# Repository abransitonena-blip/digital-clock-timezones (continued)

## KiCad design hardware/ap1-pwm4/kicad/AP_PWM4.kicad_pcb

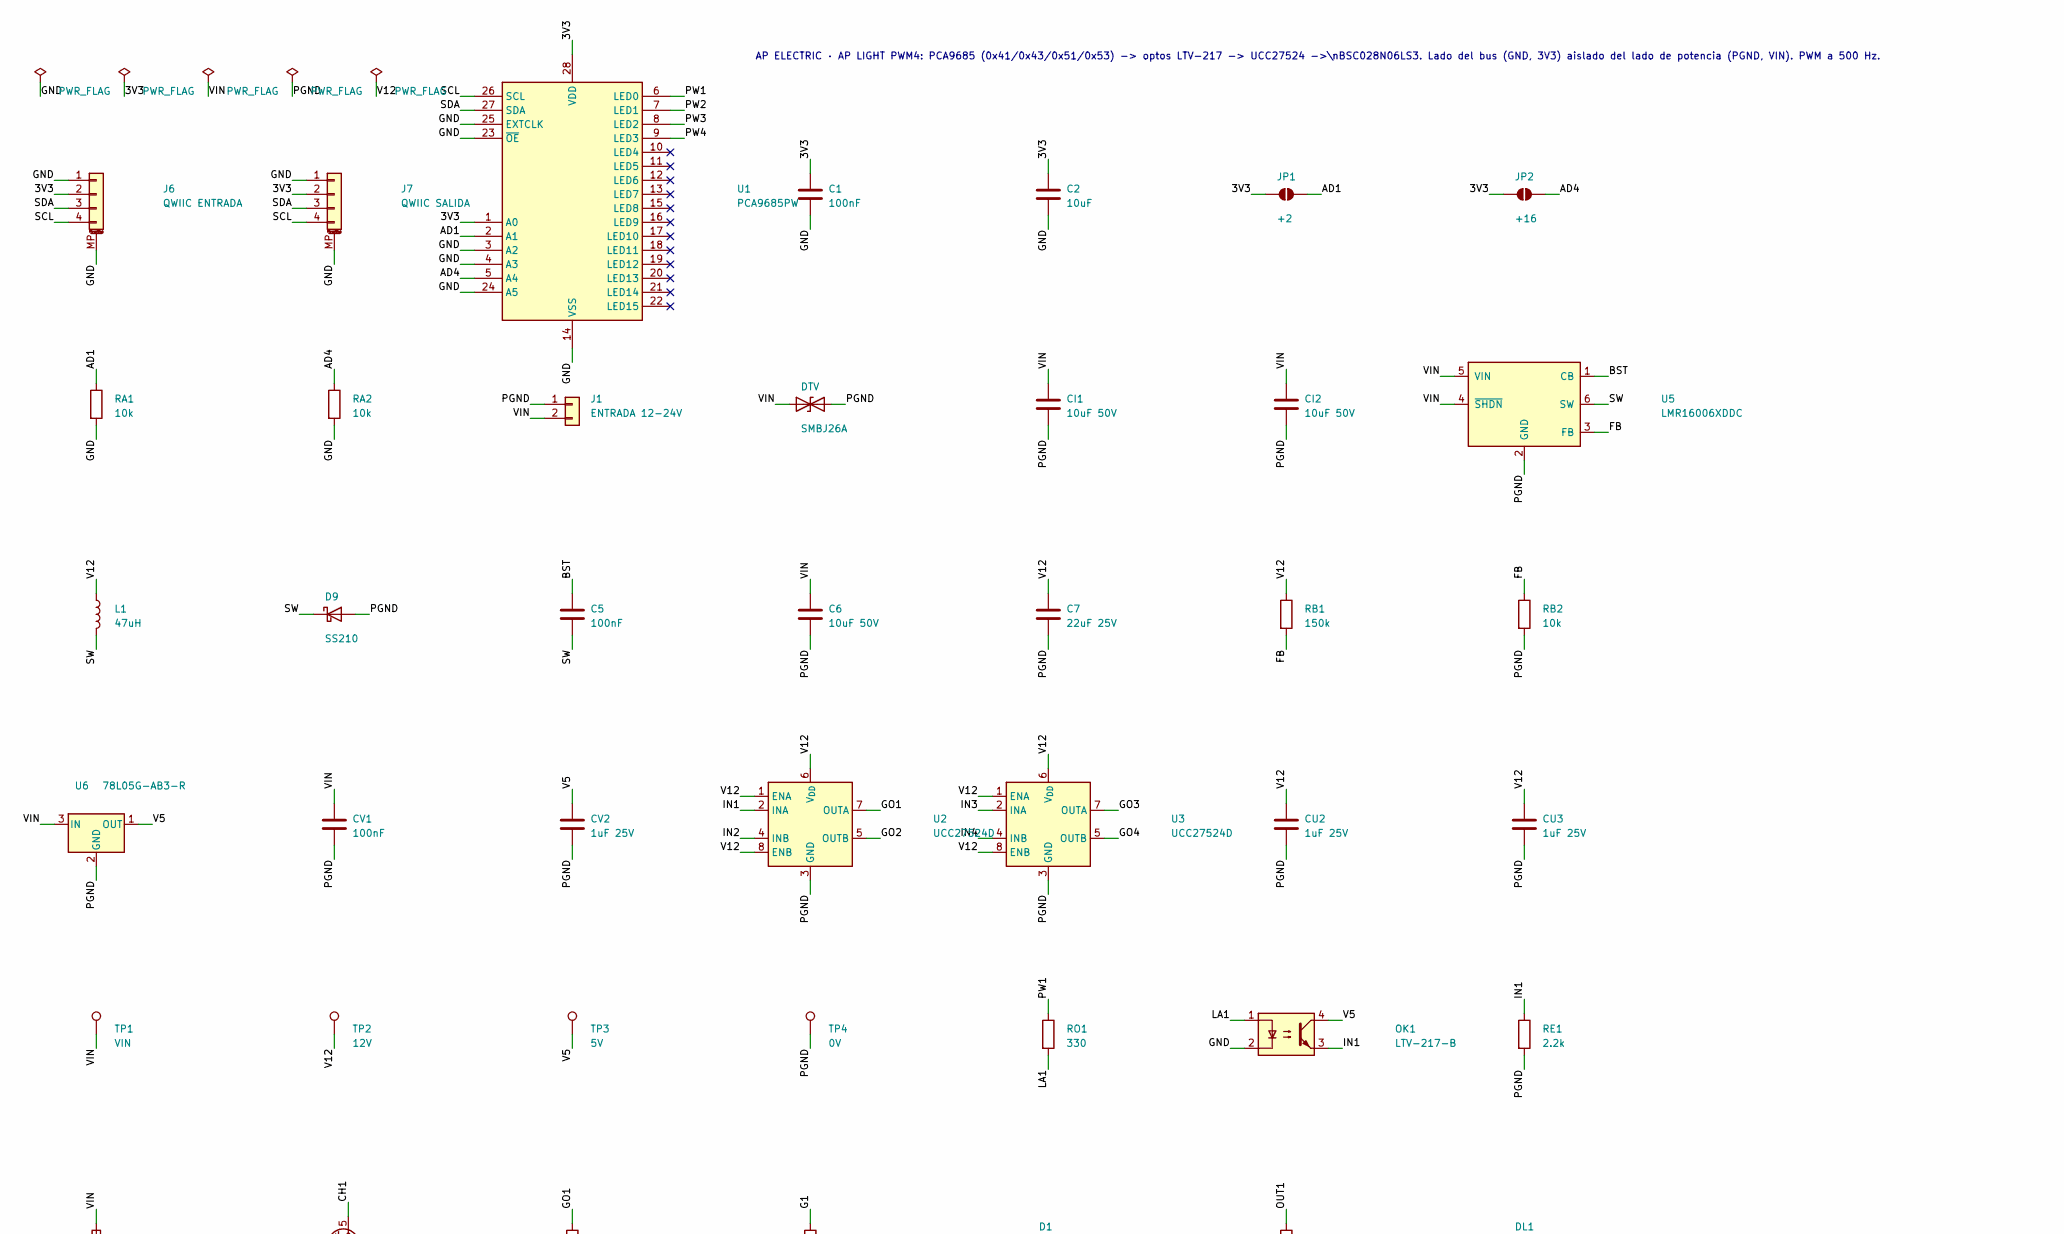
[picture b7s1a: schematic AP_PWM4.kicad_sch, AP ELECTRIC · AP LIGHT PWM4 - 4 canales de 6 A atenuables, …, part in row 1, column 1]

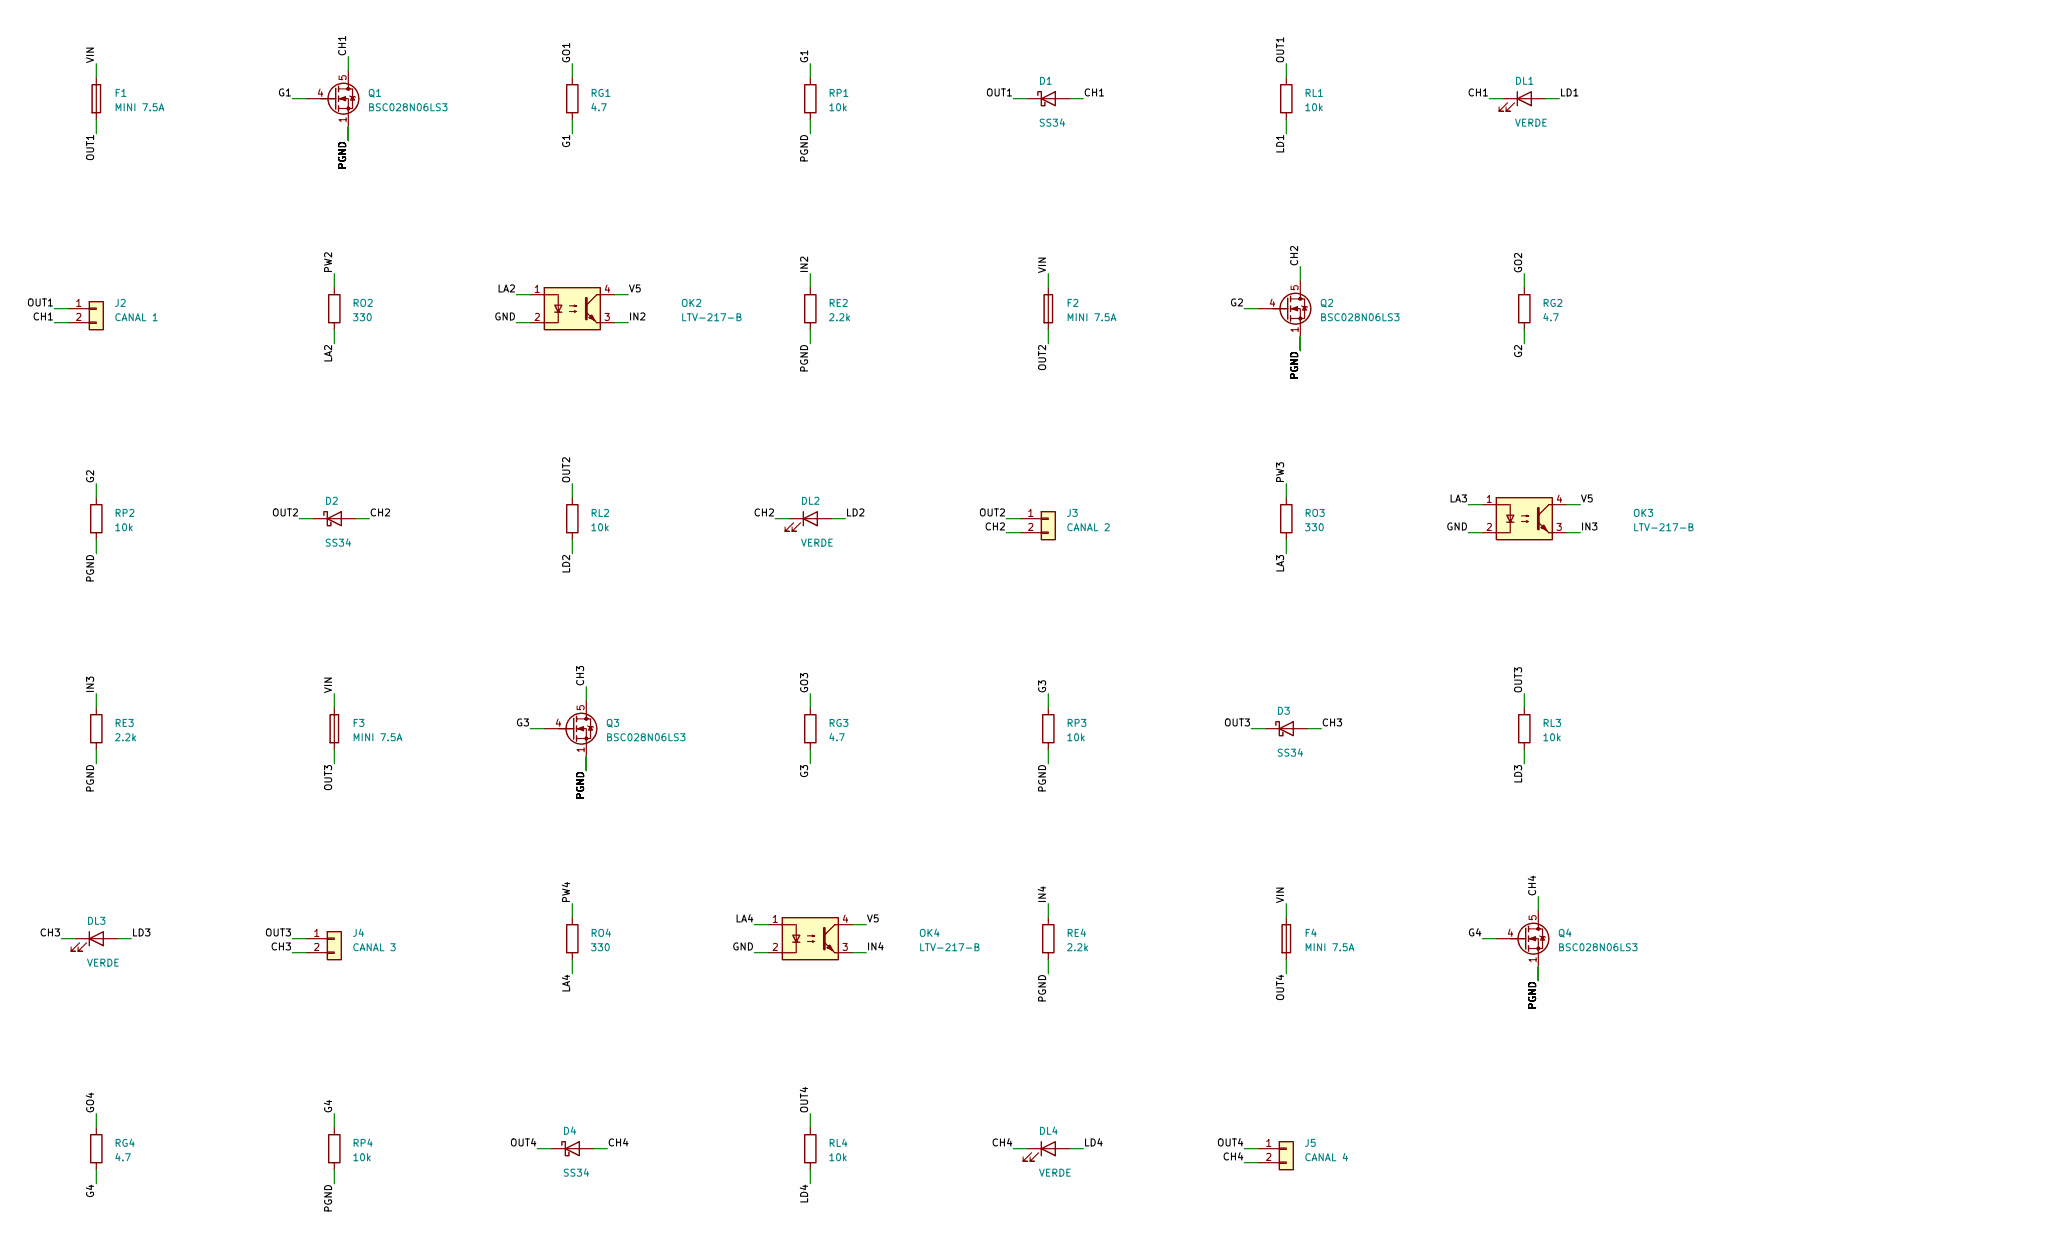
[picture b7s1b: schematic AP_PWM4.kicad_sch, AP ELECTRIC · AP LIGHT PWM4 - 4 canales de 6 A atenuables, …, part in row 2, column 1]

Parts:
C1, C5: 100nF; C_0603_1608Metric
C2: 10uF; C_0805_2012Metric
C6: 10uF 50V; C_1206_3216Metric
C7: 22uF 25V; C_1206_3216Metric
CI1, CI2: 10uF 50V; C_1206_3216Metric
CU2, CU3: 1uF 25V; C_0603_1608Metric
CV1: 100nF; C_0603_1608Metric
CV2: 1uF 25V; C_0603_1608Metric
D1, D2, D3, D4: SS34; D_SMA
D9: SS210; D_SMA
DL1, DL2, DL3, DL4: VERDE; LED_0603_1608Metric
DTV: SMBJ26A; D_SMB
F1, F2, F3, F4: MINI 7.5A; Fuseholder_Blade_Mini_Keystone_3568
J1: ENTRADA 12-24V; AMASS_XT60PW-M_1x02_P7.20mm_Horizontal
J2: CANAL 1; JST_VH_B2P-VH_1x02_P3.96mm_Vertical
J3: CANAL 2; JST_VH_B2P-VH_1x02_P3.96mm_Vertical
J4: CANAL 3; JST_VH_B2P-VH_1x02_P3.96mm_Vertical
J5: CANAL 4; JST_VH_B2P-VH_1x02_P3.96mm_Vertical
J6: QWIIC ENTRADA; JST_SH_SM04B-SRSS-TB_1x04-1MP_P1.00mm_Horizontal
J7: QWIIC SALIDA; JST_SH_SM04B-SRSS-TB_1x04-1MP_P1.00mm_Horizontal
JP1: +2; SolderJumper-2_P1.3mm_Open_RoundedPad1.0x1.5mm
JP2: +16; SolderJumper-2_P1.3mm_Open_RoundedPad1.0x1.5mm
L1: 47uH; L_Changjiang_FNR4030S
OK1, OK2, OK3, OK4: LTV-217-B; SOP-4_4.4x2.6mm_P1.27mm
Q1, Q2, Q3, Q4: BSC028N06LS3; TDSON-8-1
RA1, RA2: 10k; R_0603_1608Metric
RB1: 150k; R_0603_1608Metric
RB2: 10k; R_0603_1608Metric
RE1, RE2, RE3, RE4: 2.2k; R_0603_1608Metric
RG1, RG2, RG3, RG4: 4.7; R_0603_1608Metric
RL1, RL2, RL3, RL4: 10k; R_0805_2012Metric
RO1, RO2, RO3, RO4: 330; R_0603_1608Metric
RP1, RP2, RP3, RP4: 10k; R_0603_1608Metric
TP1: VIN; TestPoint_Pad_D1.5mm
TP2: 12V; TestPoint_Pad_D1.5mm
TP3: 5V; TestPoint_Pad_D1.5mm
TP4: 0V; TestPoint_Pad_D1.5mm
U1: PCA9685PW; TSSOP-28_4.4x9.7mm_P0.65mm
U2, U3: UCC27524D; SOIC-8_3.9x4.9mm_P1.27mm
U5: LMR16006XDDC; SOT-23-6
U6: 78L05G-AB3-R; SOT-89-3

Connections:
/3V3: C1.1, C2.1, J6.2, J7.2, JP1.1 (A), JP2.1 (A), U1.1 (A0), U1.28 (VDD)
/AD1: JP1.2 (B), RA1.1, U1.2 (A1)
/AD4: JP2.2 (B), RA2.1, U1.5 (A4)
/BST: C5.1, U5.1 (CB)
/CH1: D1.2 (A), DL1.1 (K), J2.2, Q1.5 (D)
/CH2: D2.2 (A), DL2.1 (K), J3.2, Q2.5 (D)
/CH3: D3.2 (A), DL3.1 (K), J4.2, Q3.5 (D)
/CH4: D4.2 (A), DL4.1 (K), J5.2, Q4.5 (D)
/FB: RB1.2, RB2.1, U5.3 (FB)
/G1: Q1.4 (G), RG1.2, RP1.1
/G2: Q2.4 (G), RG2.2, RP2.1
/G3: Q3.4 (G), RG3.2, RP3.1
/G4: Q4.4 (G), RG4.2, RP4.1
/GND: C1.2, C2.2, J6.1, J6.MP (MountPin), J7.1, J7.MP (MountPin), OK1.2, OK2.2, OK3.2, OK4.2, RA1.2, RA2.2, U1.3 (A2), U1.4 (A3), U1.14 (VSS), U1.23 (~OE), U1.24 (A5), U1.25 (EXTCLK)
/GO1: RG1.1, U2.7 (OUTA)
/GO2: RG2.1, U2.5 (OUTB)
/GO3: RG3.1, U3.7 (OUTA)
/GO4: RG4.1, U3.5 (OUTB)
/IN1: OK1.3, RE1.1, U2.2 (INA)
/IN2: OK2.3, RE2.1, U2.4 (INB)
/IN3: OK3.3, RE3.1, U3.2 (INA)
/IN4: OK4.3, RE4.1, U3.4 (INB)
/LA1: OK1.1, RO1.2
/LA2: OK2.1, RO2.2
/LA3: OK3.1, RO3.2
/LA4: OK4.1, RO4.2
/LD1: DL1.2 (A), RL1.2
/LD2: DL2.2 (A), RL2.2
/LD3: DL3.2 (A), RL3.2
/LD4: DL4.2 (A), RL4.2
/OUT1: D1.1 (K), F1.2, J2.1, RL1.1
/OUT2: D2.1 (K), F2.2, J3.1, RL2.1
/OUT3: D3.1 (K), F3.2, J4.1, RL3.1
/OUT4: D4.1 (K), F4.2, J5.1, RL4.1
/PGND: C6.2, C7.2, CI1.2, CI2.2, CU2.2, CU3.2, CV1.2, CV2.2, D9.2 (A), DTV.2 (A2), J1.1, Q1.1 (S), Q1.2 (S), Q1.3 (S), Q2.1 (S), Q2.2 (S), Q2.3 (S), Q3.1 (S), Q3.2 (S), Q3.3 (S), Q4.1 (S), Q4.2 (S), Q4.3 (S), RB2.2, RE1.2, RE2.2, RE3.2, RE4.2, RP1.2, RP2.2, RP3.2, RP4.2, TP4.1, U2.3 (GND), U3.3 (GND), U5.2 (GND), U6.2 (GND)
/PW1: RO1.1, U1.6 (LED0)
/PW2: RO2.1, U1.7 (LED1)
/PW3: RO3.1, U1.8 (LED2)
/PW4: RO4.1, U1.9 (LED3)
/SCL: J6.4, J7.4, U1.26 (SCL)
/SDA: J6.3, J7.3, U1.27 (SDA)
/SW: C5.2, D9.1 (K), L1.2, U5.6 (SW)
/V5: CV2.1, OK1.4, OK2.4, OK3.4, OK4.4, TP3.1, U6.1 (OUT)
/V12: C7.1, CU2.1, CU3.1, L1.1, RB1.1, TP2.1, U2.1 (ENA), U2.6 (V_{DD}), U2.8 (ENB), U3.1 (ENA), U3.6 (V_{DD}), U3.8 (ENB)
/VIN: C6.1, CI1.1, CI2.1, CV1.1, DTV.1 (A1), F1.1, F2.1, F3.1, F4.1, J1.2, TP1.1, U5.4 (~SHDN), U5.5 (VIN), U6.3 (IN)

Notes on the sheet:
AP ELECTRIC · AP LIGHT PWM4: PCA9685 (0x41/0x43/0x51/0x53) -> optos LTV-217 -> UCC27524 ->\nBSC028N06LS3. Lado del bus (GND, 3V3) aislado del lado de potencia (PGND, VIN). PWM a 500 Hz.

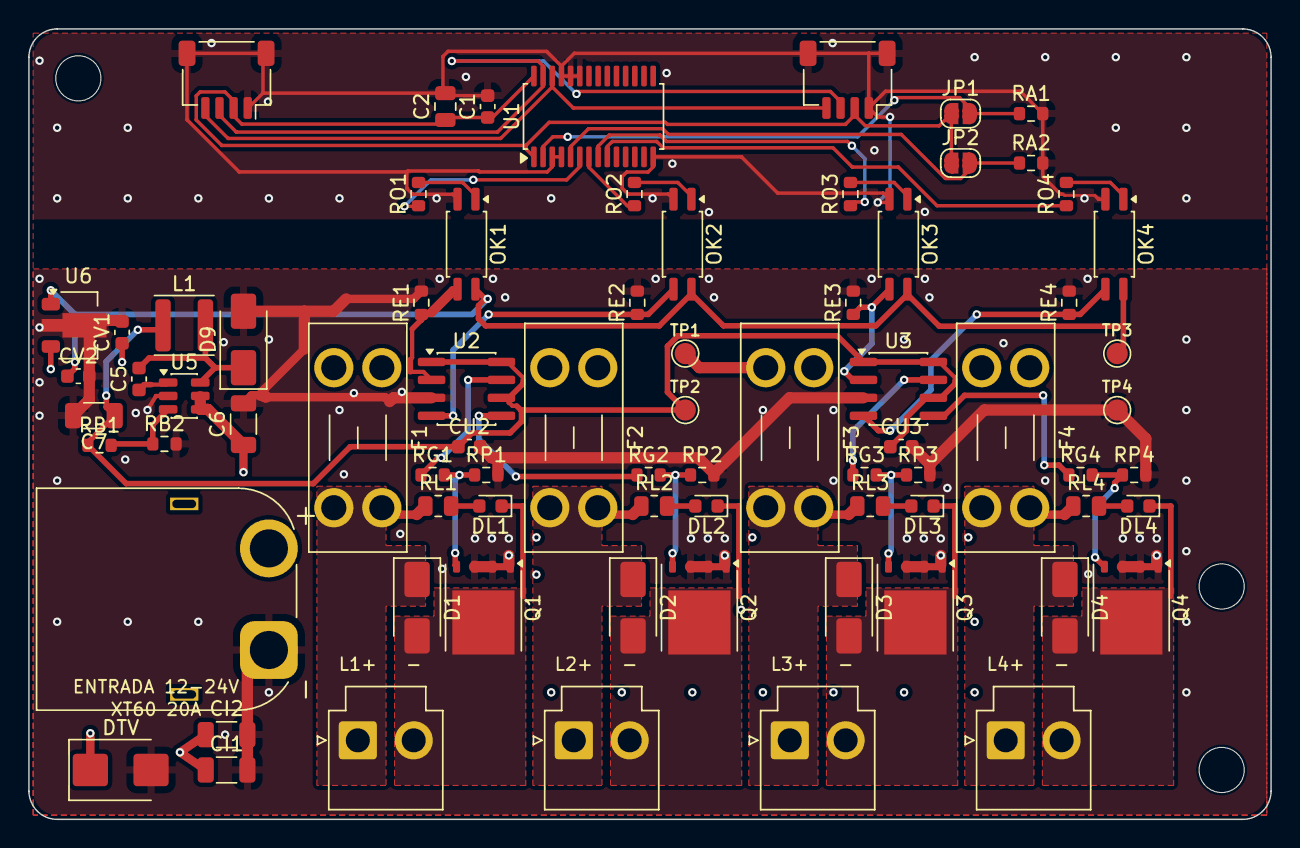
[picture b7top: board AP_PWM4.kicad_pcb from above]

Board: 4 copper layers, 88.0 x 56.0 mm, 79 parts (0 on the bottom side), 45 nets.

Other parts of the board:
H1, H2, H3: MountingHole_3.2mm_M3

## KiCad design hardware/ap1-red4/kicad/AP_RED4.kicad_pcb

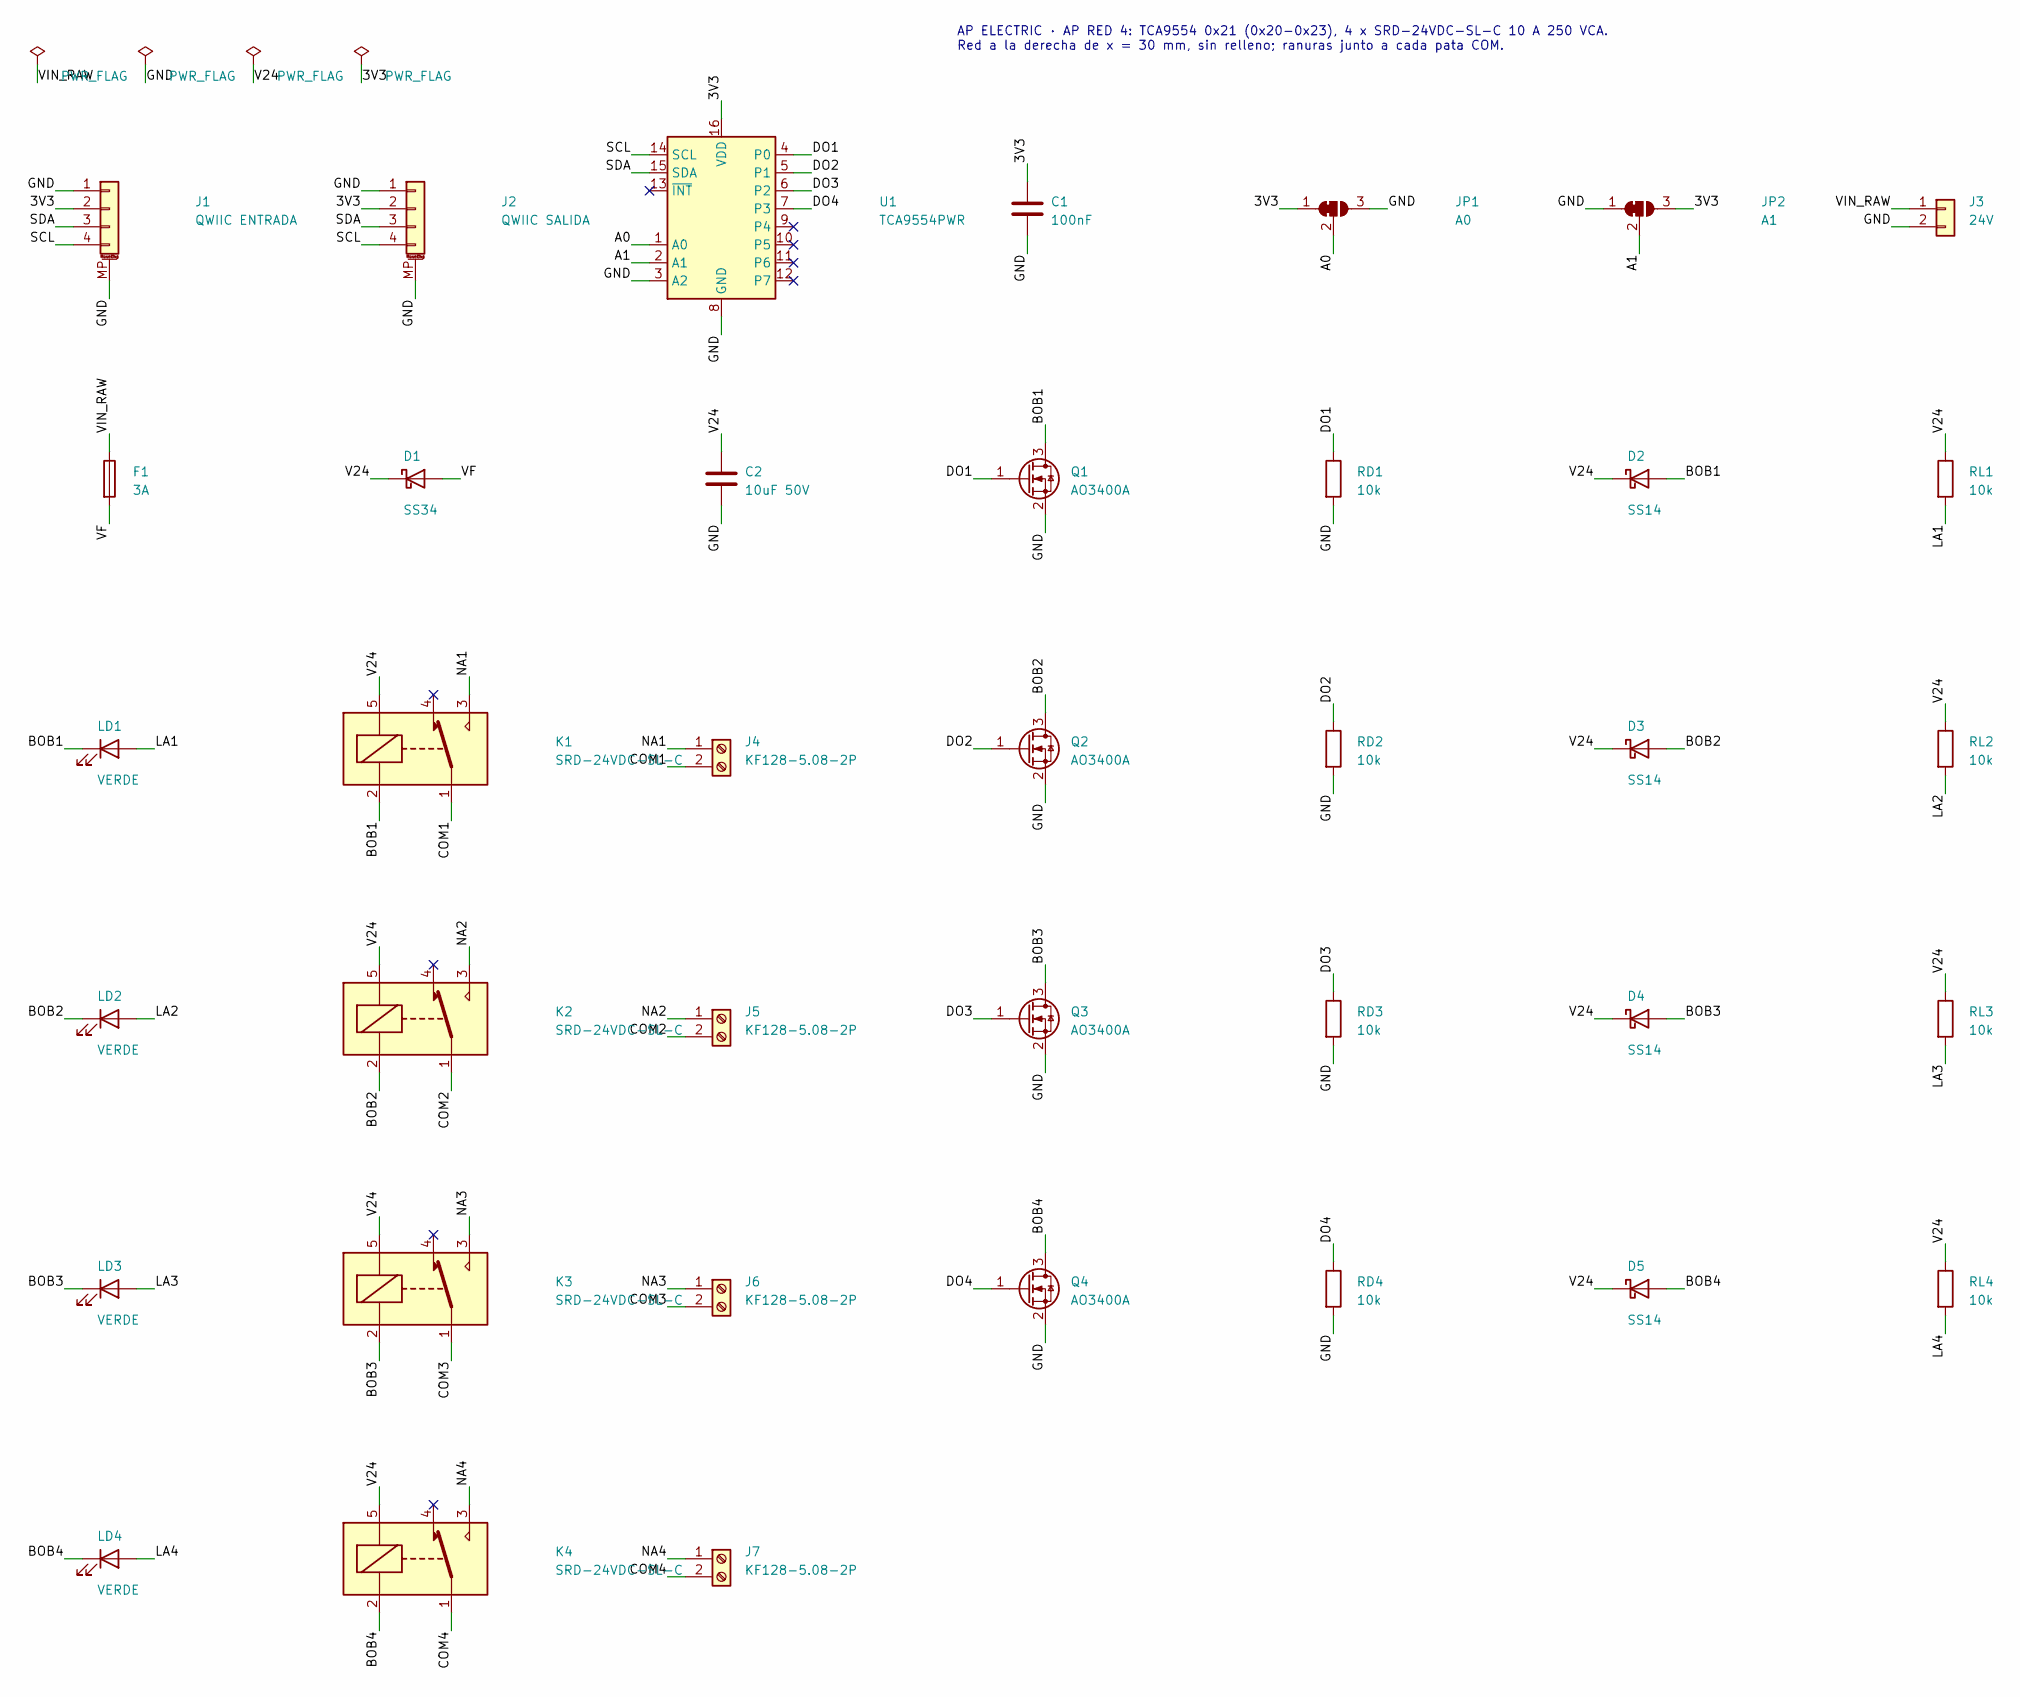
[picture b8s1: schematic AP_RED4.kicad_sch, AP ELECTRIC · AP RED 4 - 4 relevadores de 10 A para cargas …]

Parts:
C1: 100nF; C_0603_1608Metric
C2: 10uF 50V; C_1206_3216Metric
D1: SS34; D_SMA
D2, D3, D4, D5: SS14; D_SMA
F1: 3A; Fuse_1206_3216Metric
J1: QWIIC ENTRADA; JST_SH_SM04B-SRSS-TB_1x04-1MP_P1.00mm_Horizontal
J2: QWIIC SALIDA; JST_SH_SM04B-SRSS-TB_1x04-1MP_P1.00mm_Horizontal
J3: 24V; JST_VH_B2P-VH_1x02_P3.96mm_Vertical
J4, J5, J6, J7: KF128-5.08-2P; TerminalBlock_Phoenix_MKDS-1,5-2-5.08_1x02_P5.08mm_Horizont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
JP1: A0; SolderJumper-3_P1.3mm_Bridged12_RoundedPad1.0x1.5mm
JP2: A1; SolderJumper-3_P1.3mm_Bridged12_RoundedPad1.0x1.5mm
K1, K2, K3, K4: SRD-24VDC-SL-C; Relay_SPDT_SANYOU_SRD_Series_Form_C
LD1, LD2, LD3, LD4: VERDE; LED_0603_1608Metric
Q1, Q2, Q3, Q4: AO3400A; SOT-23
RD1, RD2, RD3, RD4: 10k; R_0603_1608Metric
RL1, RL2, RL3, RL4: 10k; R_0603_1608Metric
U1: TCA9554PWR; TSSOP-16_4.4x5mm_P0.65mm

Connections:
/3V3: C1.1, J1.2, J2.2, JP1.1 (A), JP2.3 (B), U1.16 (VDD)
/A0: JP1.2 (C), U1.1 (A0)
/A1: JP2.2 (C), U1.2 (A1)
/BOB1: D2.2 (A), K1.2, LD1.1 (K), Q1.3 (D)
/BOB2: D3.2 (A), K2.2, LD2.1 (K), Q2.3 (D)
/BOB3: D4.2 (A), K3.2, LD3.1 (K), Q3.3 (D)
/BOB4: D5.2 (A), K4.2, LD4.1 (K), Q4.3 (D)
/COM1: J4.2, K1.1
/COM2: J5.2, K2.1
/COM3: J6.2, K3.1
/COM4: J7.2, K4.1
/DO1: Q1.1 (G), RD1.1, U1.4 (P0)
/DO2: Q2.1 (G), RD2.1, U1.5 (P1)
/DO3: Q3.1 (G), RD3.1, U1.6 (P2)
/DO4: Q4.1 (G), RD4.1, U1.7 (P3)
/GND: C1.2, C2.2, J1.1, J1.MP (MountPin), J2.1, J2.MP (MountPin), J3.2, JP1.3 (B), JP2.1 (A), Q1.2 (S), Q2.2 (S), Q3.2 (S), Q4.2 (S), RD1.2, RD2.2, RD3.2, RD4.2, U1.3 (A2), U1.8 (GND)
/LA1: LD1.2 (A), RL1.2
/LA2: LD2.2 (A), RL2.2
/LA3: LD3.2 (A), RL3.2
/LA4: LD4.2 (A), RL4.2
/NA1: J4.1, K1.3
/NA2: J5.1, K2.3
/NA3: J6.1, K3.3
/NA4: J7.1, K4.3
/SCL: J1.4, J2.4, U1.14 (SCL)
/SDA: J1.3, J2.3, U1.15 (SDA)
/V24: C2.1, D1.1 (K), D2.1 (K), D3.1 (K), D4.1 (K), D5.1 (K), K1.5, K2.5, K3.5, K4.5, RL1.1, RL2.1, RL3.1, RL4.1
/VF: D1.2 (A), F1.2
/VIN_RAW: F1.1, J3.1

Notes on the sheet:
AP ELECTRIC · AP RED 4: TCA9554 0x21 (0x20-0x23), 4 x SRD-24VDC-SL-C 10 A 250 VCA. Red a la derecha de x = 30 mm, sin relleno; ranuras junto a cada pata COM.

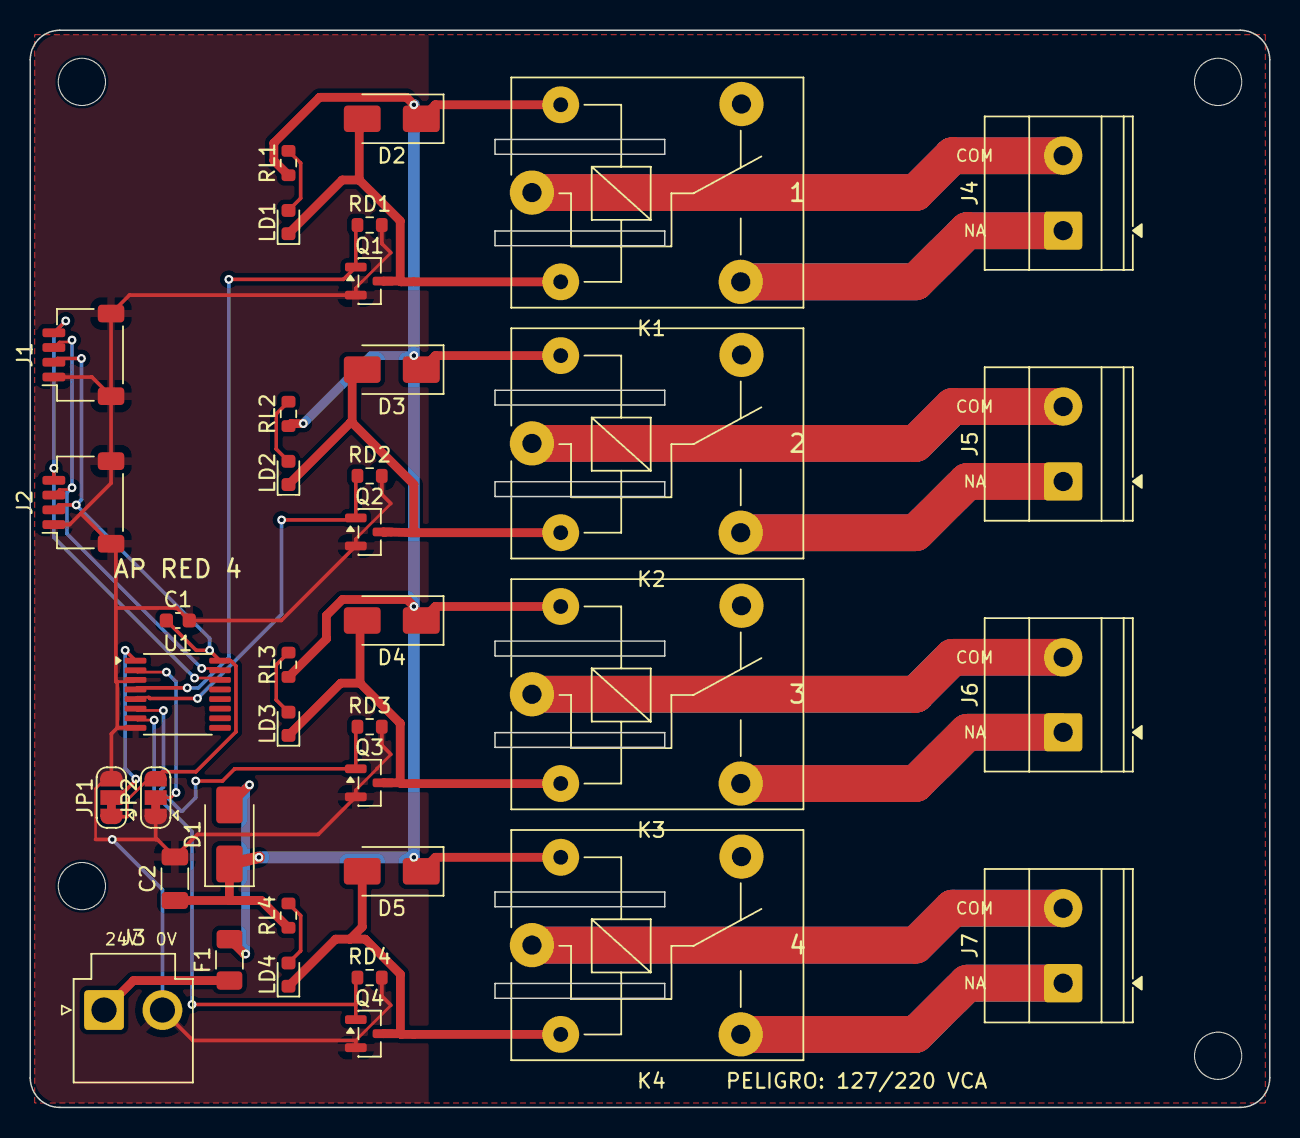
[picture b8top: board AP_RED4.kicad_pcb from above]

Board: 2 copper layers, 84.0 x 73.0 mm, 42 parts (0 on the bottom side), 29 nets.

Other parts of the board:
H1, H2, H3, H4: MountingHole_3.2mm_M3
